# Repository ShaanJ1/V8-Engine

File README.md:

# V8 Engine
A 3D printed V8 engine powered by a DC motor (NOTE: The motor control PCB does not work as of now, but you're still able to spin the engine manually or use the full speed of the motor)

### Note:
Make sure to lubricate all moving parts to prevent damage to your 3D print. This project was made assuming that this will be printed in ABS, PETG, or another heat-resistant material. If you are using a material like PLA, note that the friction at high speeds may cause the print to very quicky melt, warp, or damage itself in another way.

### Showcase
*Coming soon...*

# Bill of Materials (BOM)

| **Item Name**                | **URL**                                                                                                                   | **Price** | **Quantity** | **Use**                         |
| ---------------------------- | ------------------------------------------------------------------------------------------------------------------------- | --------: | -----------: | ------------------------------- |
| 3D Printing Filament         | [Amazon](https://www.amazon.ca/dp/B09DKMW78Y)                                                                             |   $105.06 |      3 x 1KG | 3D filament used (ABS)          |
| 12V Battery                  | [Amazon](https://a.co/d/iR5ZKYJ)                                                                                          |    $33.38 |            1 | Power Source                    |
| DC Motor                     | [AliExpress](https://www.aliexpress.com/item/1005008221484428.html)                                                       |    $17.89 |            1 | Spinning Engine                 |
| Silicone Grease              | [AliExpress](https://www.aliexpress.com/item/1005008374157659.html)                                                       |     $3.65 |            1 | Lubricant for moving parts      |
| Heat Shrink                  | [AliExpress](https://www.aliexpress.com/item/1005008146302901.html)                                                       |     $3.62 |            1 | For exposed soldered wires      |
| PCB                          | [JLCPCB](https://jlcpcb.com/)                                                                                             |     $4.78 |            1 | Main Controller                 |
| M3 10mm Set Screws           | [AliExpress](https://www.aliexpress.com/item/4001081433504.html)                                                          |     $2.79 |            1 | Main Assembly + Flywheel Screws |
| M4 6mm Screws                | [AliExpress](https://www.aliexpress.com/item/1005001785690381.html)                                                       |     $2.76 |            1 | Motor Mounting Screws           |
| M4 16mm Set Screws           | [AliExpress](https://www.aliexpress.com/item/1005008512534705.html)                                                       |     $4.69 |            1 | Connecting Rod Screws           |
| M8 25mm Screws               | [AliExpress](https://www.aliexpress.com/item/1005006090579821.html)                                                       |     $4.07 |            1 | Output Gear Holder              |
| 5x8 Shaft Coupler            | [AliExpress](https://www.aliexpress.com/item/1005006305848755.html)                                                       |     $6.91 |            1 | Motor to Gear Coupler           |
| 608ZZ Bearing                | [AliExpress](https://www.aliexpress.com/item/1005010525419357.html)                                                       |     $4.35 |            1 | Spins output gear               |
| 18 AWG Wires (2 ft)          | [DigiKey](https://www.digikey.ca/en/products/detail/te-connectivity-aerospace-defense-and-marine/FLHTC0311-18-0/6061732)  |     $4.00 |         2 ft | Wiring                          |
| 100µF Electrolytic Capacitor | [DigiKey](https://www.digikey.ca/en/products/detail/w%C3%BCrth-elektronik/860020473008/5727062)                           |     $0.19 |            1 | Decoupling                      |
| 0.1µF 0805 Ceramic Capacitor | [DigiKey](https://www.digikey.ca/en/products/detail/kemet/C0805F104K1RACAUTO/26735352)                                    |     $0.33 |            1 | Decoupling                      |
| MBR2045CT                    | [DigiKey](https://www.digikey.ca/en/products/detail/smc-diode-solutions/MBR2045CT/6022134)                                |     $1.97 |            1 | Motor Flywheeling Diode         |
| SS14                         | [DigiKey](https://www.digikey.ca/en/products/detail/taiwan-semiconductor-corporation/SS14/7369347)                        |     $0.68 |            2 | Diodes                          |
| Green LED                    | [DigiKey](https://www.digikey.ca/en/products/detail/w-rth-elektronik/151051VS04000/4490015)                               |     $0.38 |            1 | ON LED                          |
| 1206 Fuse 7A 32V             | [DigiKey](https://www.digikey.ca/en/products/detail/schurter-inc/3413-0326-22/2644167)                                    |     $2.34 |            3 | Circuit Protection              |
| 1x2 Terminal Block           | [DigiKey](https://www.digikey.ca/en/products/detail/te-connectivity-amp-connectors/282837-2/2187973)                      |     $2.20 |            2 | Power Input, Motor Power        |
| IRFZ44                       | [DigiKey](https://www.digikey.ca/en/products/detail/infineon-technologies/IRFZ44NPBF/811772)                              |     $2.10 |            1 | N Channel MOSFET                |
| MMBT2222A                    | [DigiKey](https://www.digikey.ca/en/products/detail/shenzhen-slkormicro-semicon-co-ltd/MMBT2222A/25880370)                |     $0.30 |            2 | NPN transistor                  |
| IRF9540N                     | [DigiKey](https://www.digikey.ca/en/products/detail/infineon-technologies/IRF9540NPBF/812088)                             |     $2.89 |            1 | P Channel MOSFET                |
| 1K 0402 Resistor             | [DigiKey](https://www.digikey.ca/en/products/detail/panasonic-electronic-components/ERJ-2RKF1001X/79729)                  |     $0.44 |           10 | Resistors                       |
| 1K 0603 Resistor             | [DigiKey](https://www.digikey.ca/en/products/detail/stackpole-electronics-inc/RMCF0603FT1K00/1761077)                     |     $0.11 |           10 | Resistors                       |
| 4.7K 0402 Resistor           | [DigiKey](https://www.digikey.ca/en/products/detail/yageo/RC0402FR-074K7L/2827563)                                        |     $0.16 |           10 | LED Resistors                   |
| 10K 0402 Resistor            | [DigiKey](https://www.digikey.ca/en/products/detail/yageo/RC0402JR-0710KL/726418)                                         |     $0.10 |           10 | Resistors                       |
| 10K 0603 Resistor            | [DigiKey](https://www.digikey.ca/en/products/detail/yageo/RC0603FR-0710KL/726880)                                         |     $0.10 |           10 | Resistors                       |
| NE555P                       | [DigiKey](https://www.digikey.ca/en/products/detail/texas-instruments/NE555P/277057)                                      |     $0.81 |            1 | 555 Timer for PWM               |
| AOD4185                      | [DigiKey](https://www.digikey.ca/en/products/detail/alpha-omega-semiconductor-inc/AOD4185/2353887)                        |     $1.82 |            1 | Circuit Protection              |
| 0805 LED                     | [DigiKey](https://www.digikey.ca/en/products/detail/w%C3%BCrth-elektronik/150080GS75000/4489915)                          |     $0.30 |            1 | Onboard LED                     |
| 10K Potentiometer            | [DigiKey](https://www.digikey.ca/en/products/detail/bourns-inc/PDB181-K425K-103B/3820304)                                 |     $1.94 |            1 | Speed Adjuster                  |
| PushButton                   | [DigiKey](https://www.digikey.ca/en/products/detail/same-sky-formerly-cui-devices-/TS02-66-55-BK-160-LCR-D/15634374)      |     $0.32 |            2 | Start/Stop Buttons              |

#### <ins>Totals (not including taxes or shipping)</ins>

**Total (CAD):** $217.43

**Total (USD):** $158.35

### Images
Schematic

PCB

Main Assembly

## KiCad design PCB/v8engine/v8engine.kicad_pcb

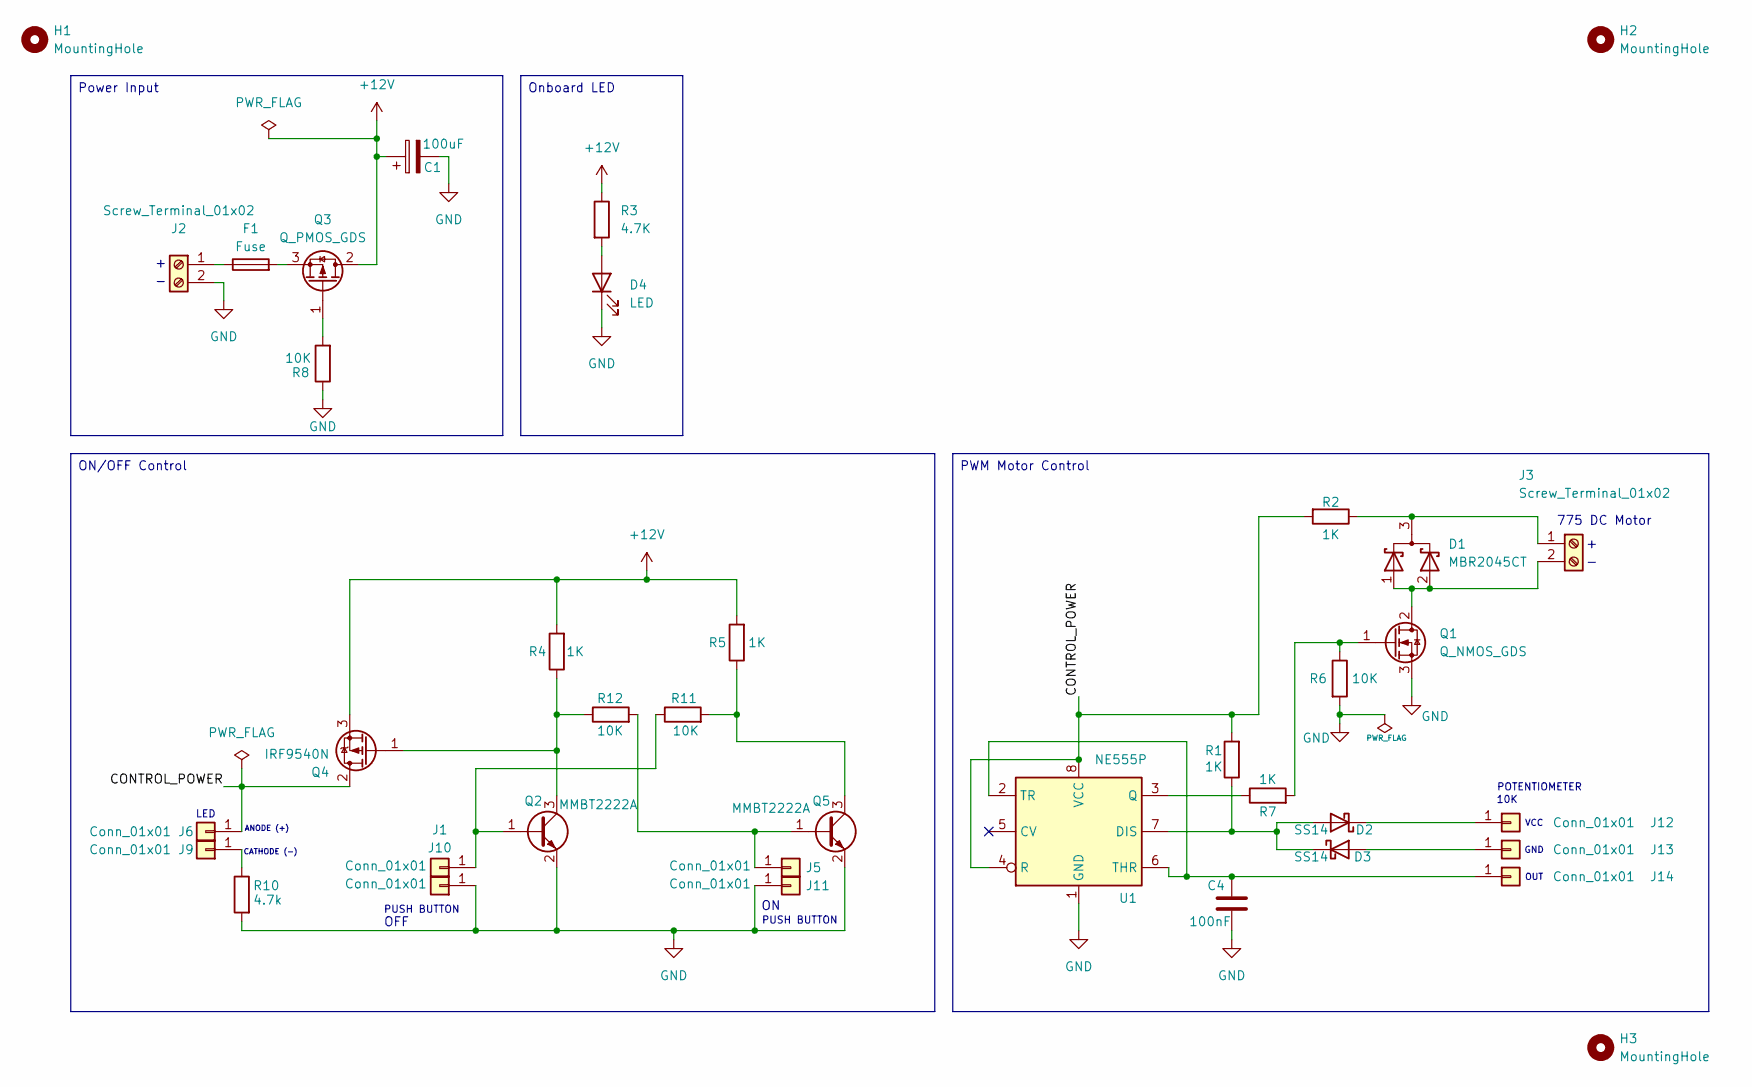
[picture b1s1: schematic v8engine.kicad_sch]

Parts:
C1: 100uF; C_Radial_D6.3mm_H11.0mm_P2.50mm
C4: 100nF; C_0805_2012Metric_Pad1.18x1.45mm_HandSolder
D1: MBR2045CT; TO-220-3_Vertical
D2, D3: SS14; D_SMA_Handsoldering
D4: LED; LED_0805_2012Metric_Pad1.15x1.40mm_HandSolder
F1: Fuse; Fuse_1206_3216Metric_Pad1.42x1.75mm_HandSolder
H1, H2, H3: MountingHole; MountingHole_2.7mm_M2.5
J1, J5, J6, J9, J10, J11, J12, J13, J14: Conn_01x01; SolderWire-0.5sqmm_1x01_D0.9mm_OD2.1mm
J2, J3: Screw_Terminal_01x02; TerminalBlock_Phoenix_MKDS-1,5-2-5.08_1x02_P5.08mm_Horizont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
Q1: Q_NMOS_GDS; TO-220-3_Vertical
Q2, Q5: MMBT2222A; SOT-23
Q3: Q_PMOS_GDS; TO-252-2
Q4: IRF9540N; TO-220-3_Vertical
R1, R2, R5, R7: 1K; R_0402_1005Metric_Pad0.72x0.64mm_HandSolder
R3: 4.7K; R_0402_1005Metric_Pad0.72x0.64mm_HandSolder
R4: 1K; R_0603_1608Metric_Pad0.98x0.95mm_HandSolder
R6, R8, R11: 10K; R_0402_1005Metric_Pad0.72x0.64mm_HandSolder
R10: 4.7k; R_0402_1005Metric_Pad0.72x0.64mm_HandSolder
R12: 10K; R_0603_1608Metric_Pad0.98x0.95mm_HandSolder
U1: NE555P; DIP-8_W7.62mm

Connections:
+12V: C1.1, Q3.2 (D), Q4.3 (S), R3.1, R4.2, R5.2
/CONTROL_POWER: J6.1, Q4.2 (D), R1.2, R2.2, U1.4 (R), U1.8 (VCC)
GND: C1.2, C4.2, D4.1 (K), J2.2, J10.1, J11.1, Q1.3 (S), Q2.2 (E), Q5.2 (E), R6.2, R8.1, R10.2, U1.1 (GND)
unnamed: D1.3 (K), J3.1, R2.1
unnamed: D2.2 (A), D3.1 (K), R1.1, U1.7 (DIS)
unnamed: D2.1 (K), J12.1
unnamed: D3.2 (A), J13.1
unnamed: D4.2 (A), R3.2
unnamed: J1.1, Q2.1 (B), R11.1
unnamed: F1.1, J2.1
unnamed: D1.1 (A), D1.2 (A), J3.2, Q1.2 (D)
unnamed: J5.1, Q5.1 (B), R12.2
unnamed: J9.1, R10.1
unnamed: C4.1, J14.1, U1.2 (TR), U1.6 (THR)
unnamed: Q1.1 (G), R6.1, R7.2
unnamed: Q2.3 (C), Q4.1 (G), R4.1, R12.1
unnamed: Q3.1 (G), R8.2
unnamed: F1.2, Q3.3 (S)
unnamed: Q5.3 (C), R5.1, R11.2
unnamed: R7.1, U1.3 (Q)

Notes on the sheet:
PUSH BUTTON
LED
775 DC Motor
VCC
GND
OUT
10K
POTENTIOMETER
ANODE (+)
CATHODE (-)
OFF
Onboard LED
PWM Motor Control
ON/OFF Control
Power Input

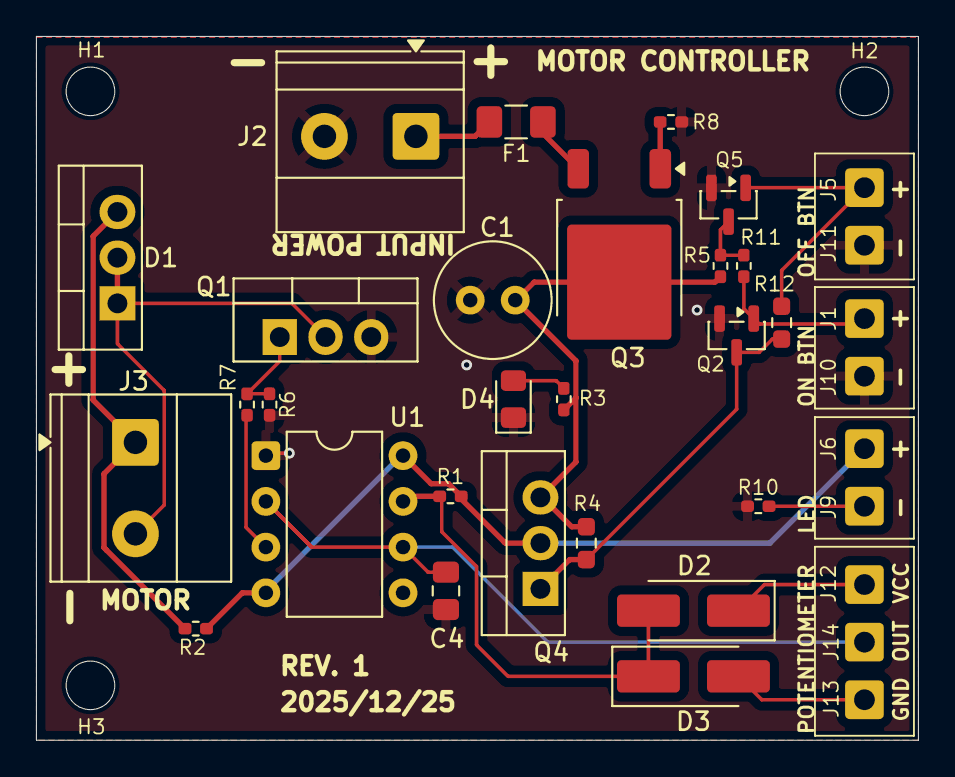
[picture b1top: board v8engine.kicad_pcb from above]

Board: 2 copper layers, 49.0 x 39.1 mm, 38 parts (0 on the bottom side), 20 nets.

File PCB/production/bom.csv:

Designator,Footprint,Quantity,Value,LCSC Part #
C1,C_Radial_D6.3mm_H11.0mm_P2.50mm,1,100uF,
C4,0805,1,100nF,
D1,TO-220-3_Vertical,1,MBR2045CT,
"D2, D3",D_SMA_Handsoldering,2,SS14,
D4,0805,1,LED,
F1,1206,1,Fuse,
"J1, J10, J11, J12, J13, J14, J5, J6, J9",SolderWire-0.5sqmm_1x01_D0.9mm_OD2.1mm,9,Conn_01x01,
"J2, J3","TerminalBlock_Phoenix_MKDS-1,5-2-5.08_1x02_P5.08mm_Horizontal",2,Screw_Terminal_01x02,
Q1,TO-220-3_Vertical,1,Q_NMOS_GDS,
"Q2, Q5",SOT-23,2,MMBT2222A,
Q3,TO-252-2,1,Q_PMOS_GDS,
Q4,TO-220-3_Vertical,1,IRF9540N,
"R1, R2, R5, R7",0402,4,1K,
"R10, R3",0402,2,4.7k,
"R11, R6, R8",0402,3,10K,
R12,0603,1,10K,
R4,0603,1,1K,
U1,DIP-8_W7.62mm,1,NE555P,

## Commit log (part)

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2025-12-26 upload
2025-12-26 update bom
2026-01-01 Adding filament costs
2026-01-02 Added 3D printing filament costs
2026-01-02 update filament costs
